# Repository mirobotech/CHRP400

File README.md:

# CHRP4

CHRP4 (Common Hardware Robotics Project 4, rev. 0) KiCad schematic and PCB design files.

CHRP4 is a simple, versatile, and inexpensive microcontroller development system designed to help anyone make simple line-following, obstacle-sensing, or Sumo robots! CHRP4 is a robot-focused derivative of [UBMP4](https://mirobo.tech/chrp4), and was designed for learning or teaching PICmicro programming for robotic applications using either Microchip’s MPLAB X IDE or the cloud-based MPLAB Xpress IDE.

CHRP4 uses the [USB µC bootloader](https://hackaday.io/project/63204-usb-c-usb-pic-bootloader), which allows CHRP4 to appear as a mass storage drive for ease of programming. Simply drag and drop a compiled .hex file onto the ***PIC16F1459*** drive that shows up in your computer's device manager, and your program will start to run as soon as the file is transferred. The bootloader makes it possible to program CHRP4 using almost any kind of device, even enabling schools with 1:1 Chromebook programs to teach real C language microcontroller programming with Github integration.

The CHRP4 circuit board has a variety of simple I/O devices built-in so beginners can learn to code and make an assortment of different projects using just the parts on CHRP4 – no breadboarding, shields, or other modules are required. The on-board components allow CHRP4 to be built in a variety of configurations including: a minimal parts, education-focused trainer for specifically for teaching or learning microcontroller programming, a simple line-following robot, and, with the addition of an ultrasonic distance sensor module, an obstacle-sensing or Sumo robot.

## CHRP4 Hardware Features

- Microchip PIC16F1459 USB-capable microcontroller with 8k words of program FLASH (6k words free when using the USB bootloader), 128B of user FLASH, 1kB of RAM, 10-bit ADC, and a built-in temperature sensor
- optional SN754410 (or L293D) quad half-H bridge motor driver to run two DC motors in forward and reverse
- optional LF50AB low drop-out regulator for 6-12V battery operation
- 5 built-in pushbuttons
- 5 visible light LEDs
- 1 piezo beeper output
- optional 4-pin header for PORTC I/O pin expansion (designed for an HC-SR04 ultrasonic SONAR module, but can also connect to servos, optical sensors, NeoPixels, etc.)
- optional IR LED and phototransistor circuits integrated on three mini, break-away modules (one designed for line following robots, two designed for general floor sensing)
- optional IR demodulator for remote control decoding
- USB 2.0 type-C port for power and programming
- 6-pin ICSP (In-Circuit Serial Programming) header for PICkit-4

Find out more at [mirobo.tech/chrp4 ](https://mirobo.tech/chrp4), and see the CHRP4 description on [Hackaday](https://hackaday.io/project/190407-chrp4-usb-robotics-development-board).

## CHRP4 is Open

CHRP4 is open hardware and uses open source software – we want educators to have full access to the circuit, lesson materials, and code. The following permissions and conditions apply to CHRP4:
- the KiCad CHRP4 files stored in GitHub are open hardware licensed under the terms of the MIT license (except the mirobo.tech logo - see below). You are free to use and modify the CHRP4 files to make your own CHRP4 circuit boards.
- CHRP4 programs stored in GitHub are open source software licensed under the terms of the MIT license.
- CHRP4 learning materials on the mirobo.tech website are licensed under the terms of the Creative Commons CC-BY 4.0 license.
- the USB uC bootloader is open source and licensed under the terms of the GPL3.0 license by John Izzard.
- the mirobo.tech logo mark is a trademark of mirobo Technolgy and may not be used without prior permission.

## Can I buy a CHRP4?

CHRP4 boards, and kits are available at [mirobo.tech](https://mirobo.tech/chrp4).  
Bare CHRP4 printed circuit boards are also available from [OSHPARK](https://oshpark.com/shared_projects/rMynSTCb).

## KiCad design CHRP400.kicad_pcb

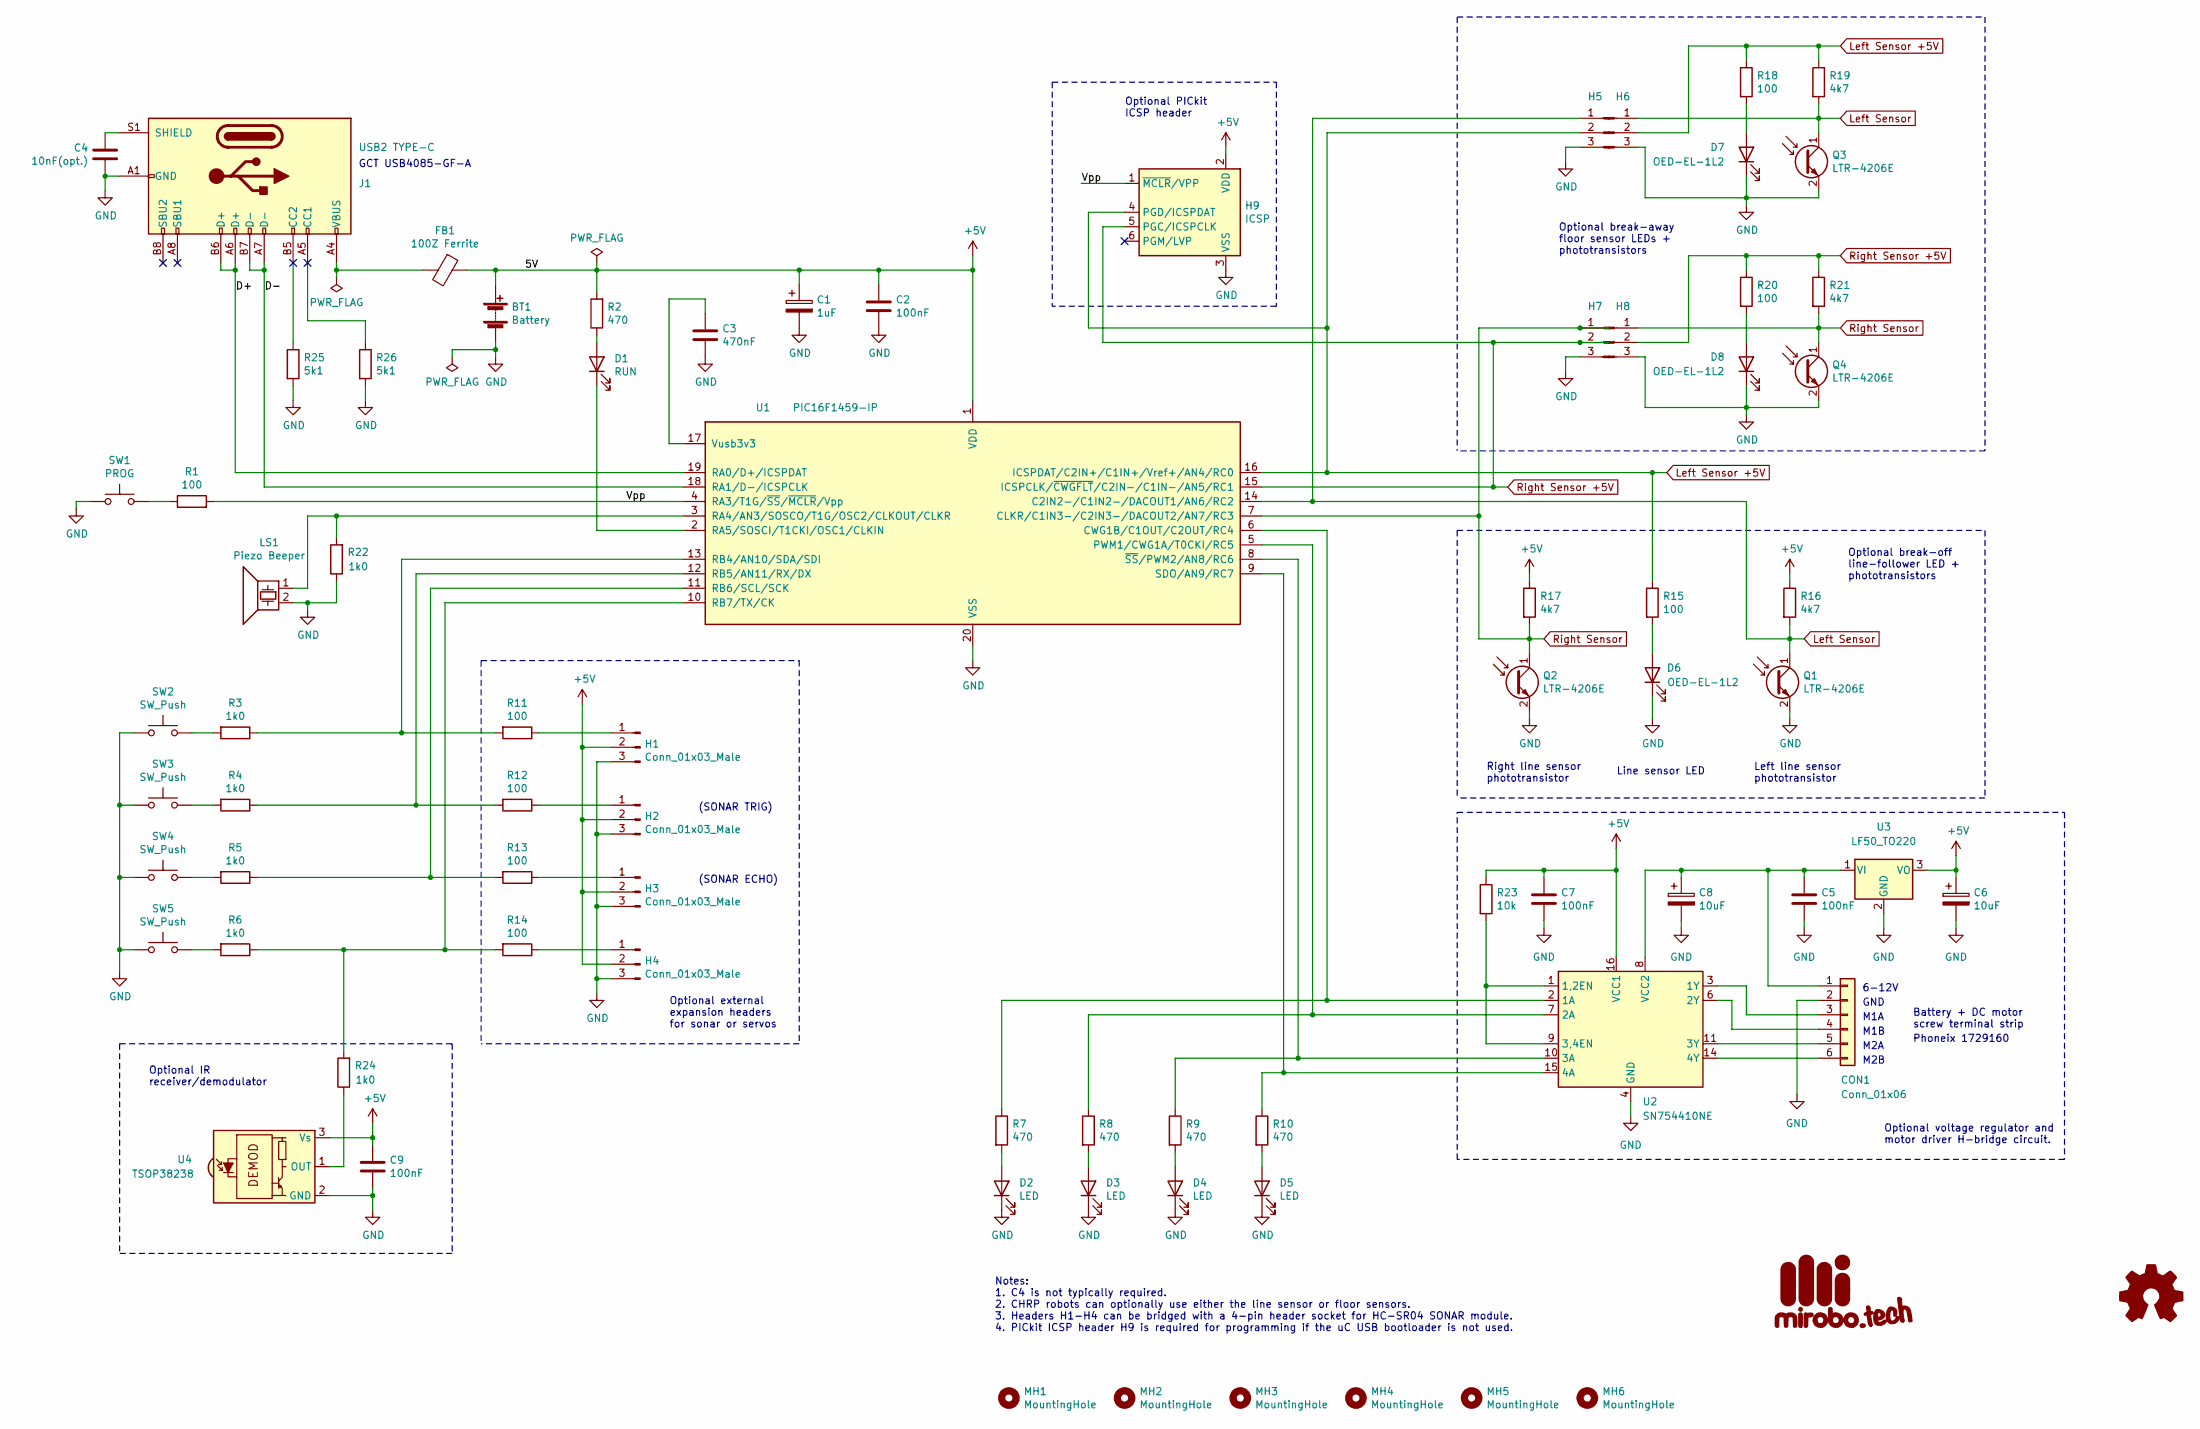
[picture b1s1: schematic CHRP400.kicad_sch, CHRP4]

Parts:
BT1: Battery; PinHeader_1x02_P2.54mm_Vertical
C1: 1uF; CP_Radial_D5.0mm_P2.50mm
C2, C5, C7, C9: 100nF; C_Disc_D3.4mm_W2.1mm_P2.50mm
C3: 470nF; C_Disc_D3.4mm_W2.1mm_P2.50mm
C4: 10nF(opt.); C_Disc_D3.4mm_W2.1mm_P2.50mm
C6, C8: 10uF; CP_Radial_D5.0mm_P2.50mm
CON1: Conn_01x06; TerminalBlock_Phoenix_MKDS-1,5-6-5.08_1x06_P5.08mm_Horizont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
D1: RUN; LED_D3.0mm
D2, D3, D4, D5: LED; LED_D3.0mm
D6, D7, D8: OED-EL-1L2; LED_D5.0mm_Clear
FB1: 100Z Ferrite; R_Axial_DIN0411_L9.9mm_D3.6mm_P12.70mm_Horizontal
G1: mirobotech_logo; mirobo_logo_10
G2: Logo_Open_Hardware_Small; OSHW-Symbol_6.7x6mm_SilkScreen
H1, H2, H3, H4, H5, H6, H7, H8: Conn_01x03_Male; PinHeader_1x03_P2.54mm_Vertical
H9: ICSP; PinHeader_1x06_P2.54mm_Horizontal
J1: USB2 TYPE-C; USB_C_Receptacle_GCT_USB4085
LS1: Piezo Beeper; Buzzer_TDK_PS1240P02BT_D12.2mm_H6.5mm
MH1, MH2, MH3, MH4, MH5, MH6: MountingHole; MountingHole_3.2mm_M3_Pad
Q1, Q2, Q3, Q4: LTR-4206E; LED_D3.0mm_IRBlack
R1, R11, R12, R13, R14, R15, R18, R20: 100; R_Axial_DIN0207_L6.3mm_D2.5mm_P10.16mm_Horizontal
R2, R7, R8, R9, R10: 470; R_Axial_DIN0207_L6.3mm_D2.5mm_P10.16mm_Horizontal
R3, R4, R5, R6, R22, R24: 1k0; R_Axial_DIN0207_L6.3mm_D2.5mm_P10.16mm_Horizontal
R16, R17, R19, R21: 4k7; R_Axial_DIN0207_L6.3mm_D2.5mm_P10.16mm_Horizontal
R23: 10k; R_Axial_DIN0207_L6.3mm_D2.5mm_P10.16mm_Horizontal
R25, R26: 5k1; R_Axial_DIN0207_L6.3mm_D2.5mm_P10.16mm_Horizontal
SW1: PROG; SW_PUSH_6mm
SW2, SW3, SW4, SW5: SW_Push; SW_PUSH_6mm
U1: PIC16F1459-IP; DIP-20_W7.62mm_Socket
U2: SN754410NE; DIP-16_W7.62mm
U3: LF50_TO220; TO-220-3_Horizontal_TabDown
U4: TSOP38238; Vishay_MINICAST-3Pin

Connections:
+5V: BT1.1 (+), C1.1, C2.1, C6.1, C7.1, C9.1, FB1.1, H1.2, H2.2, H3.2, H4.2, H9.2 (VDD), R2.2, R16.1, R17.1, R23.1, U1.1 (VDD), U2.16 (VCC1), U3.3 (VO), U4.3 (Vs)
/D+: J1.A6 (D+), J1.B6 (D+), U1.19 (RA0/D+/ICSPDAT)
/D-: J1.A7 (D-), J1.B7 (D-), U1.18 (RA1/D-/ICSPCLK)
/Vpp: H9.1 (~MCLR/VPP), R1.2, U1.4 (RA3/T1G/~SS/~MCLR/Vpp)
GND: BT1.2 (-), C1.2, C2.2, C3.2, C4.1, C5.2, C6.2, C7.2, C8.2, C9.2, CON1.2, D2.1 (K), D3.1 (K), D4.1 (K), D5.1 (K), D6.1 (K), D7.1 (K), D8.1 (K), H1.3, H2.3, H3.3, H4.3, H5.3, H6.3, H7.3, H8.3, H9.3 (VSS), J1.A1 (GND), J1.A12 (GND), J1.B1 (GND), J1.B12 (GND), LS1.2, Q1.2 (E), Q2.2 (E), Q3.2 (E), Q4.2 (E), R22.1, R25.2, R26.2, SW1.1, SW2.1, SW3.1, SW4.1, SW5.1, U1.20 (VSS), U2.4 (GND), U2.5 (GND), U2.12 (GND), U2.13 (GND), U3.2 (GND), U4.2 (GND)
Left Sensor: H5.1, H6.1, Q1.1 (C), Q3.1 (C), R16.2, R19.2, U1.14 (C2IN2-/C1IN2-/DACOUT1/AN6/RC2)
Left Sensor +5V: H5.2, H6.2, H9.4 (PGD/ICSPDAT), R15.1, R18.1, R19.1, U1.16 (ICSPDAT/C2IN+/C1IN+/Vref+/AN4/RC0)
unnamed: FB1.2, J1.A4 (VBUS), J1.A9 (VBUS), J1.B4 (VBUS), J1.B9 (VBUS)
unnamed: C5.1, C8.1, CON1.1, U2.8 (VCC2), U3.1 (VI)
unnamed: CON1.3, U2.3 (1Y)
unnamed: CON1.4, U2.6 (2Y)
unnamed: CON1.5, U2.11 (3Y)
unnamed: CON1.6, U2.14 (4Y)
unnamed: D1.2 (A), R2.1
unnamed: D1.1 (K), U1.2 (RA5/SOSCI/T1CKI/OSC1/CLKIN)
unnamed: D2.2 (A), R7.2
unnamed: D3.2 (A), R8.2
unnamed: D4.2 (A), R9.2
unnamed: D5.2 (A), R10.2
unnamed: D6.2 (A), R15.2
unnamed: D7.2 (A), R18.2
unnamed: D8.2 (A), R20.2
unnamed: H1.1, R11.1
unnamed: H2.1, R12.1
unnamed: H3.1, R13.1
unnamed: H4.1, R14.1
unnamed: C4.2, J1.S1 (SHIELD)
unnamed: R1.1, SW1.2
unnamed: R3.2, SW2.2
unnamed: R4.2, SW3.2
unnamed: R5.2, SW4.2
unnamed: R6.2, SW5.2
unnamed: R7.1, U1.6 (CWG1B/C1OUT/C2OUT/RC4), U2.2 (1A)
unnamed: R8.1, U1.5 (PWM1/CWG1A/T0CKI/RC5), U2.7 (2A)
unnamed: LS1.1, R22.2, U1.3 (RA4/AN3/SOSCO/T1G/OSC2/CLKOUT/CLKR)
unnamed: R3.1, R11.2, U1.13 (RB4/AN10/SDA/SDI)
unnamed: R4.1, R12.2, U1.12 (RB5/AN11/RX/DX)
unnamed: R5.1, R13.2, U1.11 (RB6/SCL/SCK)
unnamed: R6.1, R14.2, R24.2, U1.10 (RB7/TX/CK)
unnamed: R10.1, U1.9 (SDO/AN9/RC7), U2.15 (4A)
unnamed: C3.1, U1.17 (Vusb3v3)
unnamed: R9.1, U1.8 (~SS/PWM2/AN8/RC6), U2.10 (3A)
unnamed: R23.2, U2.1 (1,2EN), U2.9 (3,4EN)
unnamed: R24.1, U4.1 (OUT)
Right Sensor: H7.1, H8.1, Q2.1 (C), Q4.1 (C), R17.2, R21.2, U1.7 (CLKR/C1IN3-/C2IN3-/DACOUT2/AN7/RC3)
Right Sensor +5V: H7.2, H8.2, H9.5 (PGC/ICSPCLK), R20.1, R21.1, U1.15 (ICSPCLK/~CWGFLT/C2IN-/C1IN-/AN5/RC1)

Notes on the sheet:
M1A
M2B
Phoneix 1729160
(SONAR TRIG)
Line sensor LED
Left line sensor phototransistor
Notes: 1. C4 is not typically required. 2. CHRP robots can optionally use either the line sensor or floor sensors. 3. Headers H1-H4 can be bridged with a 4-pin header socket for HC-SR04 SONAR module. 4. PICkit ICSP header H9 is required for programming if the uC USB bootloader is not used.
GCT USB4085-GF-A
Optional break-off line-follower LED + phototransistors
Optional external expansion headers for sonar or servos
M1B
Optional break-away floor sensor LEDs + phototransistors
GND
Right line sensor phototransistor
(SONAR ECHO)
Optional voltage regulator and motor driver H-bridge circuit.
Optional IR receiver/demodulator
M2A
Battery + DC motor screw terminal strip
6-12V
Optional PICkit ICSP header

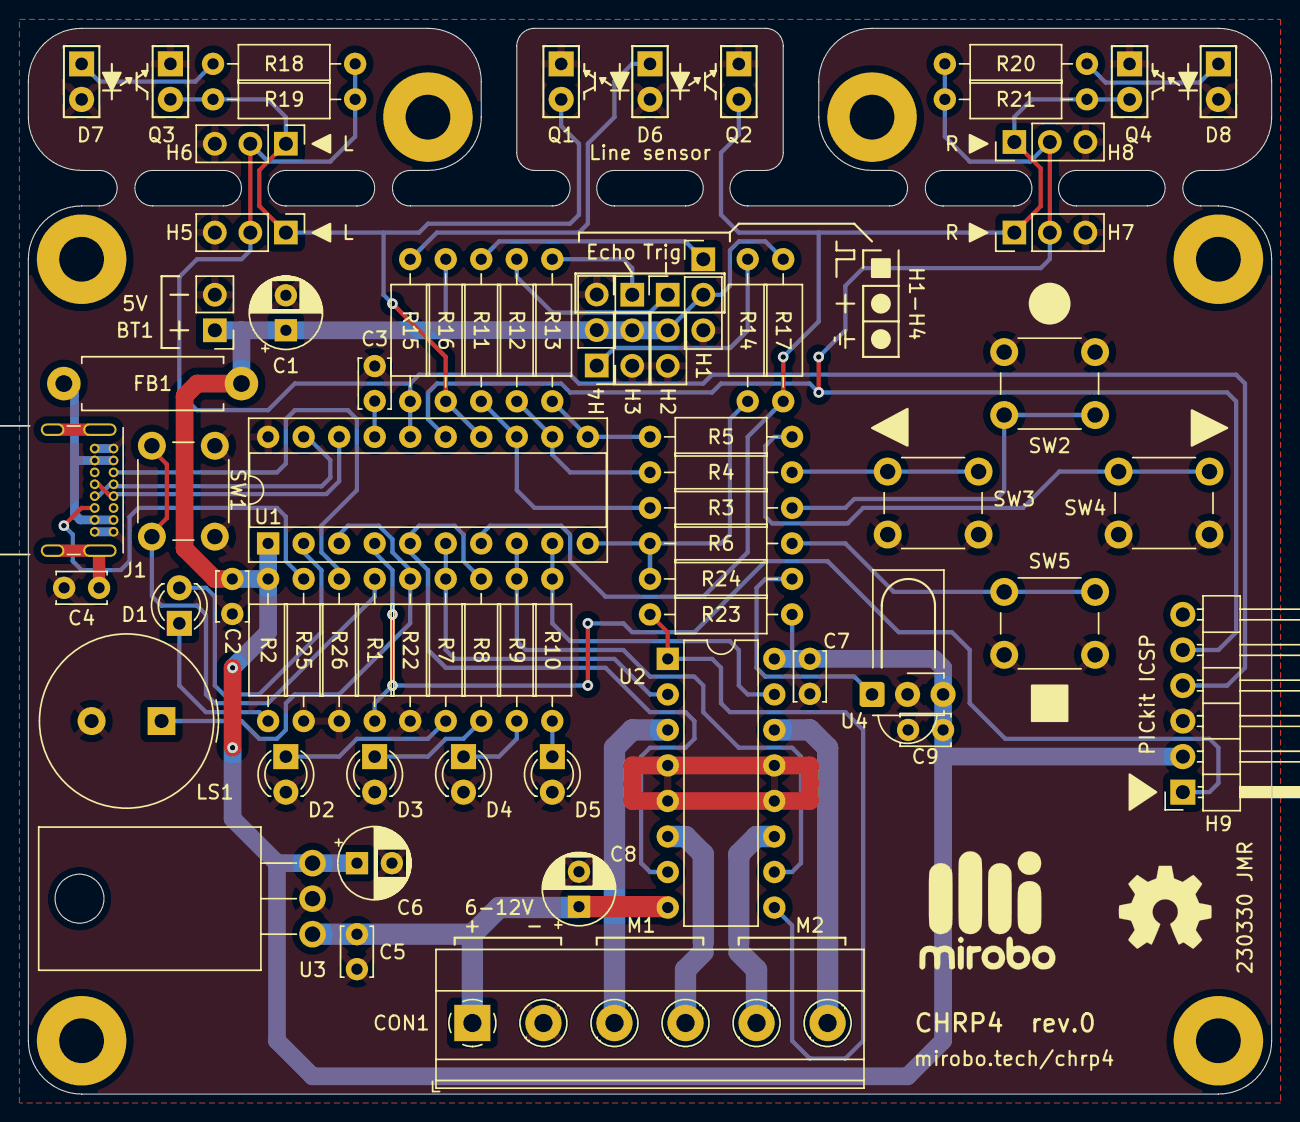
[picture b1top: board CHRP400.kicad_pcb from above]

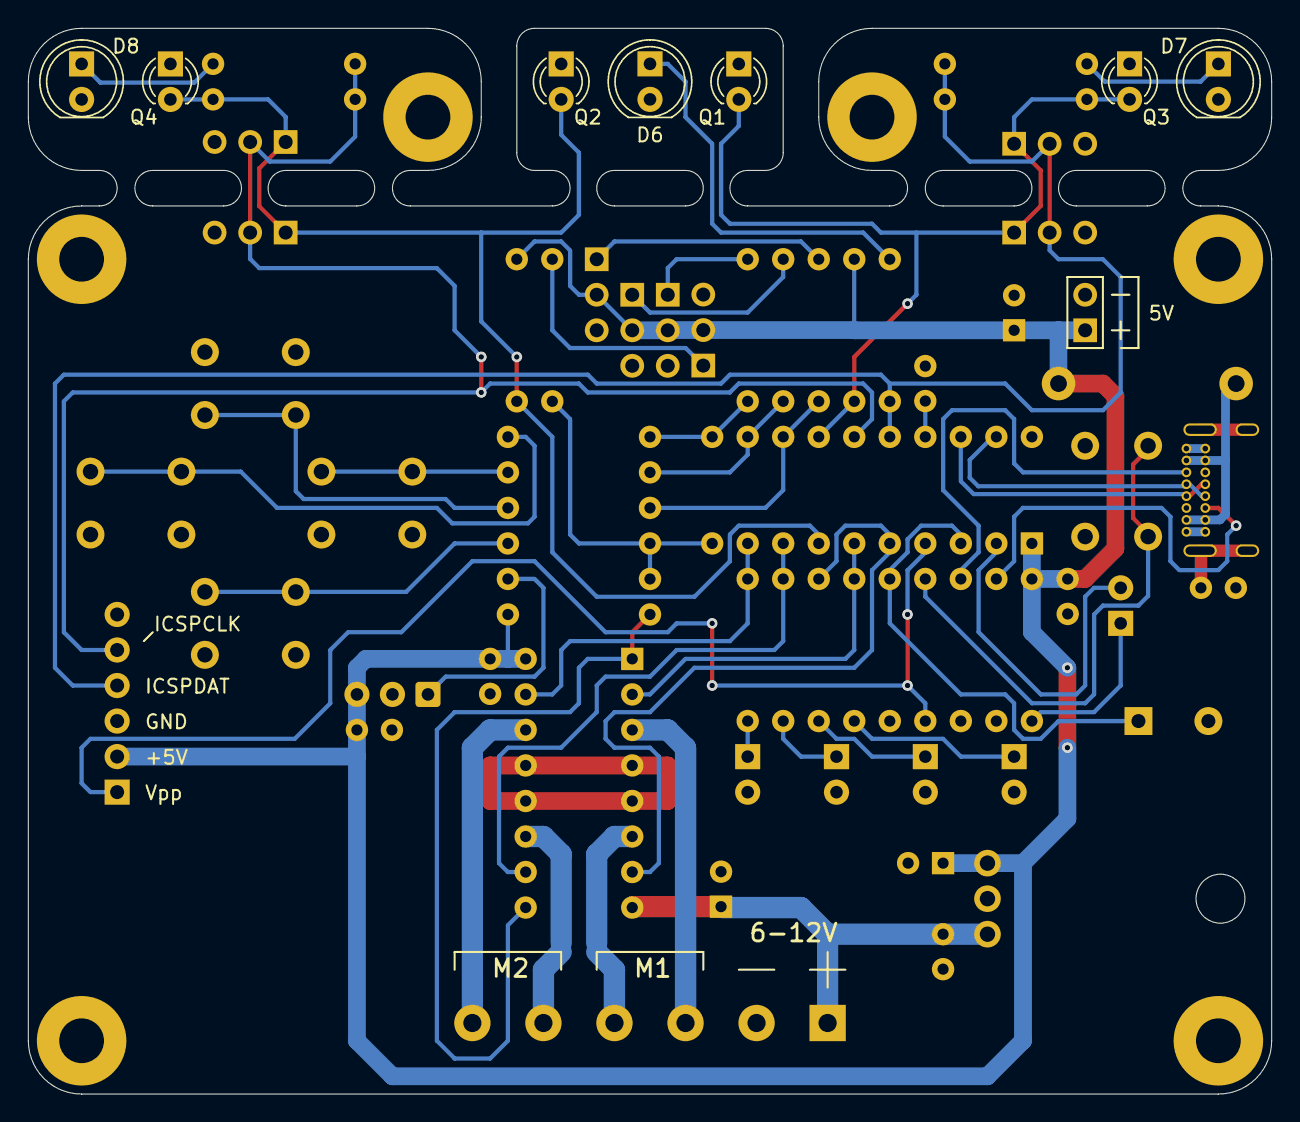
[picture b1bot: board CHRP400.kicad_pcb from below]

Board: 2 copper layers, 88.9 x 76.2 mm, 78 parts (7 on the bottom side), 46 nets.

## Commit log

2023-04-25 Add .gitignore

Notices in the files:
CHRP400.kicad_pcb:
Drawings: CC-BY 4.0
CHRP400.kicad_sch:
Schematic: CC-BY 4.0
